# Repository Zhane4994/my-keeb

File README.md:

# My custom keeb for Fabricate

Hi! This keyboard was completely made and designed by my self with RMK software. This couldn't be done without Hack Club's KEEB doc's so huge shout out to them [Check it out here!](https://keeb.hackclub.com/docs/getting-started/) 
I also created a case on onshape, you can check it out [here](https://cad.onshape.com/documents/6c549647807777fa15118c8b/w/18eee8c51750e2c3ba516c3b/e/88b95604ab3b91696ed0ff4c?renderMode=0&uiState=6ae170e70fad28d43182f47b)
----------------------
 <-- PCB HERE

This is a mechanical keyboard that I built from scratch. 

Its a really weird layout. I decided that a delete key isn't really necessary but I still want the function keys. Its similar and close to a 75 percent, so I supposes its like 70%

*Every part of this was made by me and some clarification from AI*

Features:
- 
 - The Nice!View display
 - EC11E Rotary Encoder
 - 77 Switches
 - 3D Cad case

# Challenges
 - Remaking the PCB like 3 times.
 - Keeping prices low
 - Finishing before October (pls gimme free devboard)
 - Creating a custom footprint
 - Wiring the pcb

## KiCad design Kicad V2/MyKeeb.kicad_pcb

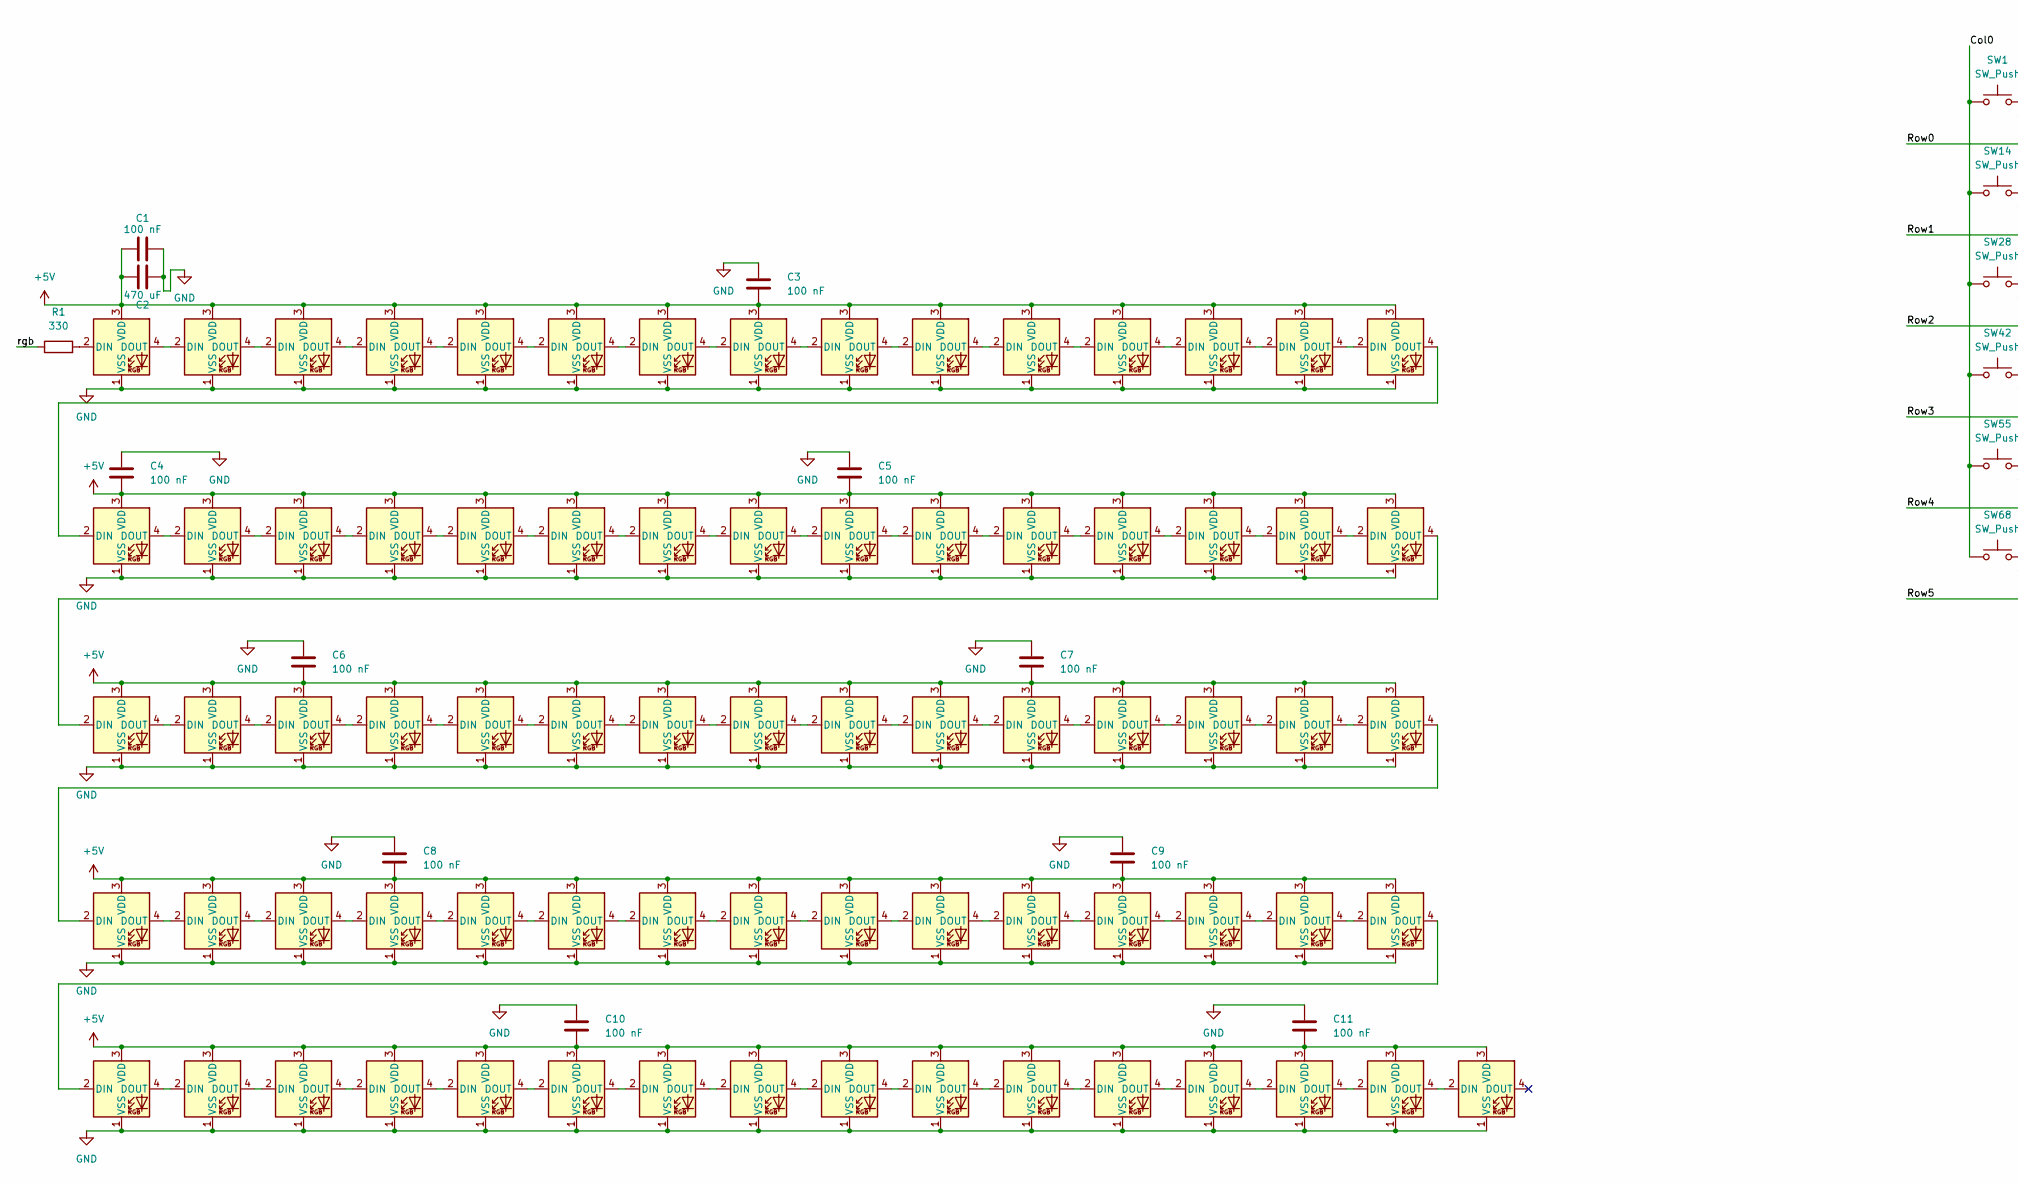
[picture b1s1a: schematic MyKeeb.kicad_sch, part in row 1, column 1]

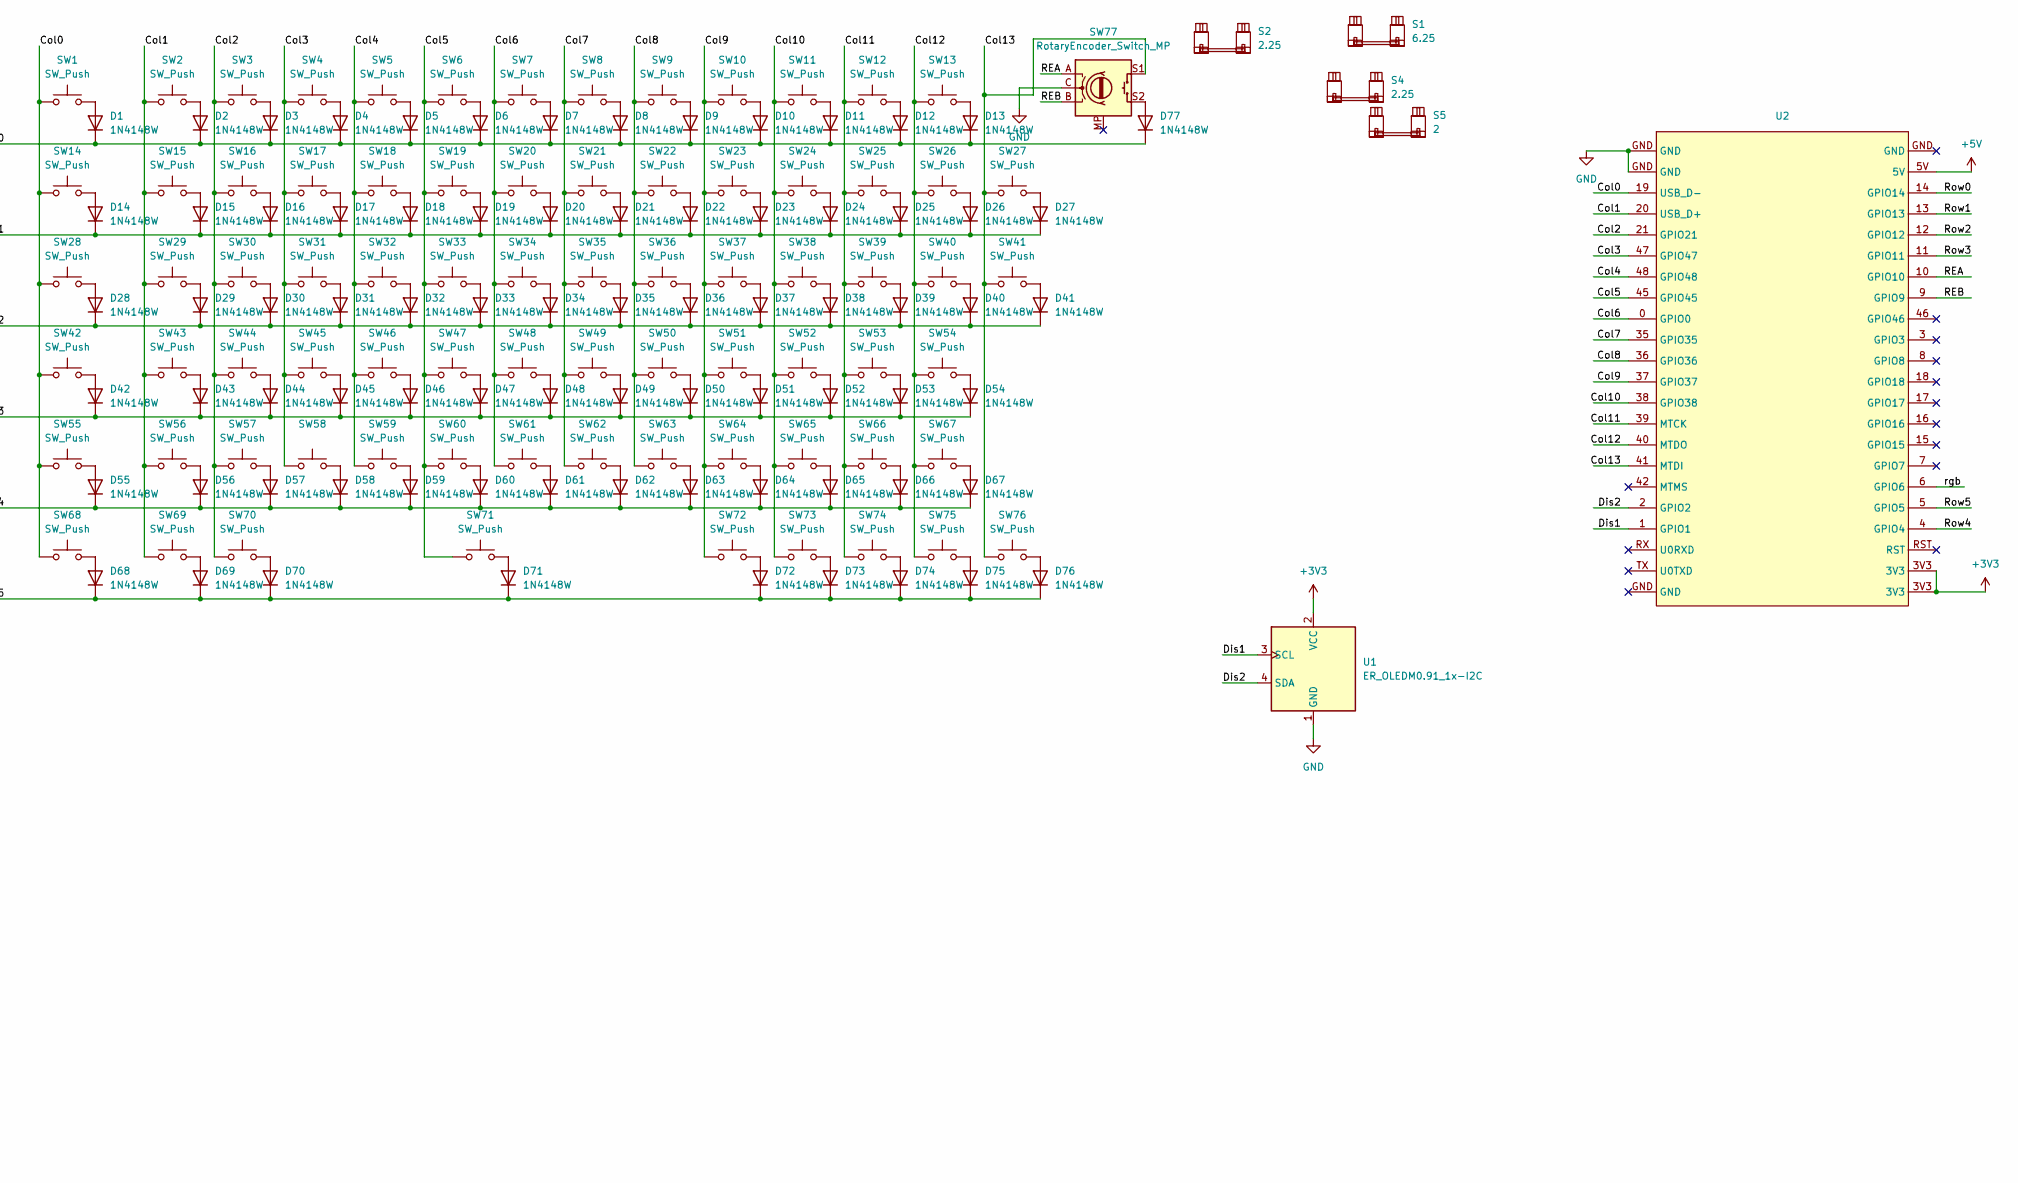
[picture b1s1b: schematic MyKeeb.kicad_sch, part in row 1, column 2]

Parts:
C1, C3, C4, C5, C6, C7, C8, C9, C10, C11: 100 nF; C_1206_3216Metric_Pad1.33x1.80mm_HandSolder
C2: 470 uF; C_Radial_D6.3mm_H7.0mm_P2.50mm
D1, D2, D3, D4, D5, D6, D7, D8, D9, D10, D11, D12, D13, D14, D15, D16, D17, D18, D19, D20, D21, D22, D23, D24, D25, D26, D27, D28, D29, D30, D31, D32, D33, D34, D35, D36, D37, D38, D39, D40, D41, D42, D43, D44, D45, D46, D47, D48, D49, D50, D51, D52, D53, D54, D55, D56, D57, D58, D59, D60, D61, D62, D63, D64, D65, D66, D67, D68, D69, D70, D71, D72, D73, D74, D75, D76, D77: 1N4148W; D_SOD-123
D78, D79, D80, D81, D82, D83, D84, D85, D86, D87, D88, D89, D90, D91, D92, D93, D94, D95, D96, D97, D98, D99, D100, D101, D102, D103, D104, D105, D106, D107, D108, D109, D110, D111, D112, D113, D114, D115, D116, D117, D118, D119, D120, D121, D122, D123, D124, D125, D126, D127, D128, D129, D130, D131, D132, D133, D134, D135, D136, D137, D138, D139, D140, D141, D142, D143, D144, D145, D146, D147, D148, D149, D150, D151, D152, D153: SK6812MINI-E; LED_MX_6028R
R1: 330; R_Axial_DIN0207_L6.3mm_D2.5mm_P10.16mm_Horizontal
S1: 6.25; STAB_MX_P_6.25u
S2, S4: 2.25; STAB_MX_2u
S5: 2; STAB_MX_2u
SW1, SW2, SW3, SW4, SW5, SW6, SW7, SW8, SW9, SW10, SW11, SW12, SW13, SW14, SW15, SW16, SW17, SW18, SW19, SW20, SW21, SW22, SW23, SW24, SW25, SW26, SW27, SW29, SW30, SW31, SW32, SW33, SW34, SW35, SW36, SW37, SW38, SW39, SW40, SW43, SW44, SW45, SW46, SW47, SW48, SW49, SW50, SW51, SW52, SW53, SW54, SW55, SW56, SW57, SW58, SW59, SW60, SW61, SW62, SW63, SW64, SW65, SW67, SW71, SW74, SW75, SW76: SW_Push; SW_MX_HS_KS-2P02B01-01_1u
SW28, SW41: SW_Push; SW_MX_HS_KS-2P02B01-01_1.5u
SW42, SW66: SW_Push; SW_MX_HS_KS-2P02B01-01_1.75u
SW68, SW69, SW70, SW72, SW73: SW_Push; SW_MX_HS_KS-2P02B01-01_1.25u
SW77: RotaryEncoder_Switch_MP; RotaryEncoder_Alps_EC11E-Switch_Vertical_H20mm_MountingHoles
U1: ER_OLEDM0.91_1x-I2C
U2: ESP32-S3-DevKit-N8R8

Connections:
+3V3: U1.2 (VCC), U2.3V3
+5V: C1.1, C2.1, C3.2, C4.2, C5.2, C6.2, C7.2, C8.2, C9.2, C10.2, C11.2, D78.3 (VDD), D79.3 (VDD), D80.3 (VDD), D81.3 (VDD), D82.3 (VDD), D83.3 (VDD), D84.3 (VDD), D85.3 (VDD), D86.3 (VDD), D87.3 (VDD), D88.3 (VDD), D89.3 (VDD), D90.3 (VDD), D91.3 (VDD), D92.3 (VDD), D93.3 (VDD), D94.3 (VDD), D95.3 (VDD), D96.3 (VDD), D97.3 (VDD), D98.3 (VDD), D99.3 (VDD), D100.3 (VDD), D101.3 (VDD), D102.3 (VDD), D103.3 (VDD), D104.3 (VDD), D105.3 (VDD), D106.3 (VDD), D107.3 (VDD), D108.3 (VDD), D109.3 (VDD), D110.3 (VDD), D111.3 (VDD), D112.3 (VDD), D113.3 (VDD), D114.3 (VDD), D115.3 (VDD), D116.3 (VDD), D117.3 (VDD), D118.3 (VDD), D119.3 (VDD), D120.3 (VDD), D121.3 (VDD), D122.3 (VDD), D123.3 (VDD), D124.3 (VDD), D125.3 (VDD), D126.3 (VDD), D127.3 (VDD), D128.3 (VDD), D129.3 (VDD), D130.3 (VDD), D131.3 (VDD), D132.3 (VDD), D133.3 (VDD), D134.3 (VDD), D135.3 (VDD), D136.3 (VDD), D137.3 (VDD), D138.3 (VDD), D139.3 (VDD), D140.3 (VDD), D141.3 (VDD), D142.3 (VDD), D143.3 (VDD), D144.3 (VDD), D145.3 (VDD), D146.3 (VDD), D147.3 (VDD), D148.3 (VDD), D149.3 (VDD), D150.3 (VDD), D151.3 (VDD), D152.3 (VDD), D153.3 (VDD), U2.5V
/Col0: SW1.1, SW14.1, SW28.1, SW42.1, SW55.1, SW68.1, U2.19 (USB_D-)
/Col1: SW2.1, SW15.1, SW29.1, SW43.1, SW56.1, SW69.1, U2.20 (USB_D+)
/Col2: SW3.1, SW16.1, SW30.1, SW44.1, SW57.1, SW70.1, U2.21 (GPIO21)
/Col3: SW4.1, SW17.1, SW31.1, SW45.1, SW58.1, U2.47 (GPIO47)
/Col4: SW5.1, SW18.1, SW32.1, SW46.1, SW59.1, U2.48 (GPIO48)
/Col5: SW6.1, SW19.1, SW33.1, SW47.1, SW60.1, SW71.1, U2.45 (GPIO45)
/Col6: SW7.1, SW20.1, SW34.1, SW48.1, SW61.1, U2.0 (GPIO0)
/Col7: SW8.1, SW21.1, SW35.1, SW49.1, SW62.1, U2.35 (GPIO35)
/Col8: SW9.1, SW22.1, SW36.1, SW50.1, SW63.1, U2.36 (GPIO36)
/Col9: SW10.1, SW23.1, SW37.1, SW51.1, SW64.1, SW72.1, U2.37 (GPIO37)
/Col10: SW11.1, SW24.1, SW38.1, SW52.1, SW65.1, SW73.1, U2.38 (GPIO38)
/Col11: SW12.1, SW25.1, SW39.1, SW53.1, SW66.1, SW74.1, U2.39 (MTCK)
/Col12: SW13.1, SW26.1, SW40.1, SW54.1, SW67.1, SW75.1, U2.40 (MTDO)
/Col13: SW27.1, SW41.1, SW76.1, SW77.S1, U2.41 (MTDI)
/Dis1: U1.3 (SCL), U2.1 (GPIO1)
/Dis2: U1.4 (SDA), U2.2 (GPIO2)
/REA: SW77.A, U2.10 (GPIO10)
/REB: SW77.B, U2.9 (GPIO9)
/Row0: D1.1 (K), D2.1 (K), D3.1 (K), D4.1 (K), D5.1 (K), D6.1 (K), D7.1 (K), D8.1 (K), D9.1 (K), D10.1 (K), D11.1 (K), D12.1 (K), D13.1 (K), D77.1 (K), U2.14 (GPIO14)
/Row1: D14.1 (K), D15.1 (K), D16.1 (K), D17.1 (K), D18.1 (K), D19.1 (K), D20.1 (K), D21.1 (K), D22.1 (K), D23.1 (K), D24.1 (K), D25.1 (K), D26.1 (K), D27.1 (K), U2.13 (GPIO13)
/Row2: D28.1 (K), D29.1 (K), D30.1 (K), D31.1 (K), D32.1 (K), D33.1 (K), D34.1 (K), D35.1 (K), D36.1 (K), D37.1 (K), D38.1 (K), D39.1 (K), D40.1 (K), D41.1 (K), U2.12 (GPIO12)
/Row3: D42.1 (K), D43.1 (K), D44.1 (K), D45.1 (K), D46.1 (K), D47.1 (K), D48.1 (K), D49.1 (K), D50.1 (K), D51.1 (K), D52.1 (K), D53.1 (K), D54.1 (K), U2.11 (GPIO11)
/Row4: D55.1 (K), D56.1 (K), D57.1 (K), D58.1 (K), D59.1 (K), D60.1 (K), D61.1 (K), D62.1 (K), D63.1 (K), D64.1 (K), D65.1 (K), D66.1 (K), D67.1 (K), U2.4 (GPIO4)
/Row5: D68.1 (K), D69.1 (K), D70.1 (K), D71.1 (K), D72.1 (K), D73.1 (K), D74.1 (K), D75.1 (K), D76.1 (K), U2.5 (GPIO5)
/rgb: R1.1, U2.6 (GPIO6)
GND: C1.2, C2.2, C3.1, C4.1, C5.1, C6.1, C7.1, C8.1, C9.1, C10.1, C11.1, D78.1 (VSS), D79.1 (VSS), D80.1 (VSS), D81.1 (VSS), D82.1 (VSS), D83.1 (VSS), D84.1 (VSS), D85.1 (VSS), D86.1 (VSS), D87.1 (VSS), D88.1 (VSS), D89.1 (VSS), D90.1 (VSS), D91.1 (VSS), D92.1 (VSS), D93.1 (VSS), D94.1 (VSS), D95.1 (VSS), D96.1 (VSS), D97.1 (VSS), D98.1 (VSS), D99.1 (VSS), D100.1 (VSS), D101.1 (VSS), D102.1 (VSS), D103.1 (VSS), D104.1 (VSS), D105.1 (VSS), D106.1 (VSS), D107.1 (VSS), D108.1 (VSS), D109.1 (VSS), D110.1 (VSS), D111.1 (VSS), D112.1 (VSS), D113.1 (VSS), D114.1 (VSS), D115.1 (VSS), D116.1 (VSS), D117.1 (VSS), D118.1 (VSS), D119.1 (VSS), D120.1 (VSS), D121.1 (VSS), D122.1 (VSS), D123.1 (VSS), D124.1 (VSS), D125.1 (VSS), D126.1 (VSS), D127.1 (VSS), D128.1 (VSS), D129.1 (VSS), D130.1 (VSS), D131.1 (VSS), D132.1 (VSS), D133.1 (VSS), D134.1 (VSS), D135.1 (VSS), D136.1 (VSS), D137.1 (VSS), D138.1 (VSS), D139.1 (VSS), D140.1 (VSS), D141.1 (VSS), D142.1 (VSS), D143.1 (VSS), D144.1 (VSS), D145.1 (VSS), D146.1 (VSS), D147.1 (VSS), D148.1 (VSS), D149.1 (VSS), D150.1 (VSS), D151.1 (VSS), D152.1 (VSS), D153.1 (VSS), SW77.C, U1.1 (GND), U2.GND
unnamed: D1.2 (A), SW1.2
unnamed: D2.2 (A), SW2.2
unnamed: D3.2 (A), SW3.2
unnamed: D4.2 (A), SW4.2
unnamed: D5.2 (A), SW5.2
unnamed: D6.2 (A), SW6.2
unnamed: D7.2 (A), SW7.2
unnamed: D8.2 (A), SW8.2
unnamed: D9.2 (A), SW9.2
unnamed: D10.2 (A), SW10.2
unnamed: D11.2 (A), SW11.2
unnamed: D12.2 (A), SW12.2
unnamed: D13.2 (A), SW13.2
unnamed: D14.2 (A), SW14.2
unnamed: D15.2 (A), SW15.2
unnamed: D16.2 (A), SW16.2
unnamed: D17.2 (A), SW17.2
unnamed: D18.2 (A), SW18.2
unnamed: D19.2 (A), SW19.2
unnamed: D20.2 (A), SW20.2
unnamed: D21.2 (A), SW21.2
unnamed: D22.2 (A), SW22.2
unnamed: D23.2 (A), SW23.2
unnamed: D24.2 (A), SW24.2
unnamed: D25.2 (A), SW25.2
unnamed: D26.2 (A), SW26.2
unnamed: D27.2 (A), SW27.2
unnamed: D28.2 (A), SW28.2
unnamed: D29.2 (A), SW29.2
unnamed: D30.2 (A), SW30.2
unnamed: D31.2 (A), SW31.2
unnamed: D32.2 (A), SW32.2
unnamed: D33.2 (A), SW33.2
unnamed: D34.2 (A), SW34.2
unnamed: D35.2 (A), SW35.2
unnamed: D36.2 (A), SW36.2
unnamed: D37.2 (A), SW37.2
unnamed: D38.2 (A), SW38.2
unnamed: D39.2 (A), SW39.2
unnamed: D40.2 (A), SW40.2
unnamed: D41.2 (A), SW41.2
unnamed: D42.2 (A), SW42.2
unnamed: D43.2 (A), SW43.2
unnamed: D44.2 (A), SW44.2
unnamed: D45.2 (A), SW45.2
unnamed: D46.2 (A), SW46.2
unnamed: D47.2 (A), SW47.2
unnamed: D48.2 (A), SW48.2
unnamed: D49.2 (A), SW49.2
unnamed: D50.2 (A), SW50.2
unnamed: D51.2 (A), SW51.2
unnamed: D52.2 (A), SW52.2
unnamed: D53.2 (A), SW53.2
unnamed: D54.2 (A), SW54.2
unnamed: D55.2 (A), SW55.2
unnamed: D56.2 (A), SW56.2
unnamed: D57.2 (A), SW57.2
unnamed: D58.2 (A), SW58.2
unnamed: D59.2 (A), SW59.2
unnamed: D60.2 (A), SW60.2
unnamed: D61.2 (A), SW61.2
unnamed: D62.2 (A), SW62.2
unnamed: D63.2 (A), SW63.2
unnamed: D64.2 (A), SW64.2
unnamed: D65.2 (A), SW65.2
unnamed: D66.2 (A), SW66.2
unnamed: D67.2 (A), SW67.2
unnamed: D68.2 (A), SW68.2
unnamed: D69.2 (A), SW69.2
unnamed: D70.2 (A), SW70.2
unnamed: D71.2 (A), SW71.2
unnamed: D72.2 (A), SW72.2
unnamed: D73.2 (A), SW73.2
unnamed: D74.2 (A), SW74.2
unnamed: D75.2 (A), SW75.2
unnamed: D76.2 (A), SW76.2
unnamed: D77.2 (A), SW77.S2
unnamed: D78.2 (DIN), R1.2
unnamed: D78.4 (DOUT), D79.2 (DIN)
unnamed: D79.4 (DOUT), D80.2 (DIN)
unnamed: D80.4 (DOUT), D81.2 (DIN)
unnamed: D81.4 (DOUT), D82.2 (DIN)
unnamed: D82.4 (DOUT), D83.2 (DIN)
unnamed: D83.4 (DOUT), D84.2 (DIN)
unnamed: D84.4 (DOUT), D85.2 (DIN)
unnamed: D85.4 (DOUT), D86.2 (DIN)
unnamed: D86.4 (DOUT), D87.2 (DIN)
unnamed: D87.4 (DOUT), D88.2 (DIN)
unnamed: D88.4 (DOUT), D89.2 (DIN)
unnamed: D89.4 (DOUT), D90.2 (DIN)
unnamed: D90.4 (DOUT), D91.2 (DIN)
unnamed: D91.4 (DOUT), D92.2 (DIN)
unnamed: D92.4 (DOUT), D93.2 (DIN)
unnamed: D93.4 (DOUT), D94.2 (DIN)
unnamed: D94.4 (DOUT), D95.2 (DIN)
unnamed: D95.4 (DOUT), D96.2 (DIN)
unnamed: D96.4 (DOUT), D97.2 (DIN)
unnamed: D97.4 (DOUT), D98.2 (DIN)
unnamed: D98.4 (DOUT), D99.2 (DIN)
unnamed: D99.4 (DOUT), D100.2 (DIN)
unnamed: D100.4 (DOUT), D101.2 (DIN)
unnamed: D101.4 (DOUT), D102.2 (DIN)
unnamed: D102.4 (DOUT), D103.2 (DIN)
unnamed: D103.4 (DOUT), D104.2 (DIN)
unnamed: D104.4 (DOUT), D105.2 (DIN)
unnamed: D105.4 (DOUT), D106.2 (DIN)
unnamed: D106.4 (DOUT), D107.2 (DIN)
unnamed: D107.4 (DOUT), D108.2 (DIN)
unnamed: D108.4 (DOUT), D109.2 (DIN)
unnamed: D109.4 (DOUT), D110.2 (DIN)
unnamed: D110.4 (DOUT), D111.2 (DIN)
unnamed: D111.4 (DOUT), D112.2 (DIN)
unnamed: D112.4 (DOUT), D113.2 (DIN)
unnamed: D113.4 (DOUT), D114.2 (DIN)
unnamed: D114.4 (DOUT), D115.2 (DIN)
unnamed: D115.4 (DOUT), D116.2 (DIN)
unnamed: D116.4 (DOUT), D117.2 (DIN)
unnamed: D117.4 (DOUT), D118.2 (DIN)
unnamed: D118.4 (DOUT), D119.2 (DIN)
unnamed: D119.4 (DOUT), D120.2 (DIN)
unnamed: D120.4 (DOUT), D121.2 (DIN)
unnamed: D121.4 (DOUT), D122.2 (DIN)
unnamed: D122.4 (DOUT), D123.2 (DIN)
unnamed: D123.4 (DOUT), D124.2 (DIN)
unnamed: D124.4 (DOUT), D125.2 (DIN)
unnamed: D125.4 (DOUT), D126.2 (DIN)
unnamed: D126.4 (DOUT), D127.2 (DIN)
unnamed: D127.4 (DOUT), D128.2 (DIN)
unnamed: D128.4 (DOUT), D129.2 (DIN)
unnamed: D129.4 (DOUT), D130.2 (DIN)
unnamed: D130.4 (DOUT), D131.2 (DIN)
unnamed: D131.4 (DOUT), D132.2 (DIN)
unnamed: D132.4 (DOUT), D133.2 (DIN)
unnamed: D133.4 (DOUT), D134.2 (DIN)
unnamed: D134.4 (DOUT), D135.2 (DIN)
unnamed: D135.4 (DOUT), D136.2 (DIN)
unnamed: D136.4 (DOUT), D137.2 (DIN)
unnamed: D137.4 (DOUT), D138.2 (DIN)
unnamed: D138.4 (DOUT), D139.2 (DIN)
unnamed: D139.4 (DOUT), D140.2 (DIN)
unnamed: D140.4 (DOUT), D141.2 (DIN)
unnamed: D141.4 (DOUT), D142.2 (DIN)
unnamed: D142.4 (DOUT), D143.2 (DIN)
unnamed: D143.4 (DOUT), D144.2 (DIN)
unnamed: D144.4 (DOUT), D145.2 (DIN)
unnamed: D145.4 (DOUT), D146.2 (DIN)
unnamed: D146.4 (DOUT), D147.2 (DIN)
unnamed: D147.4 (DOUT), D148.2 (DIN)
unnamed: D148.4 (DOUT), D149.2 (DIN)
unnamed: D149.4 (DOUT), D150.2 (DIN)
unnamed: D150.4 (DOUT), D151.2 (DIN)
unnamed: D151.4 (DOUT), D152.2 (DIN)
unnamed: D152.4 (DOUT), D153.2 (DIN)

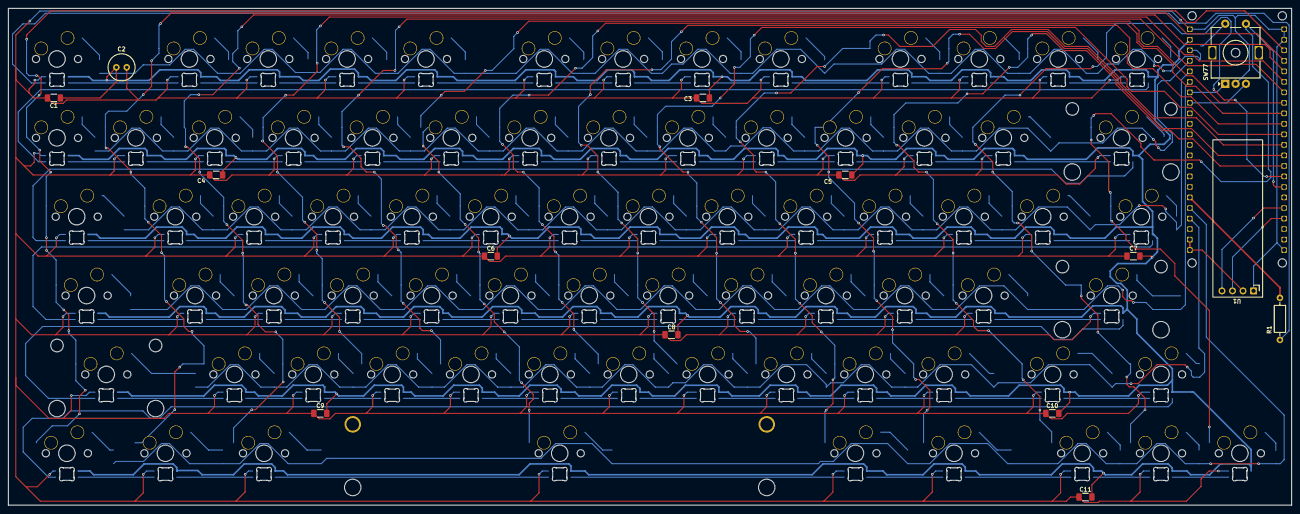
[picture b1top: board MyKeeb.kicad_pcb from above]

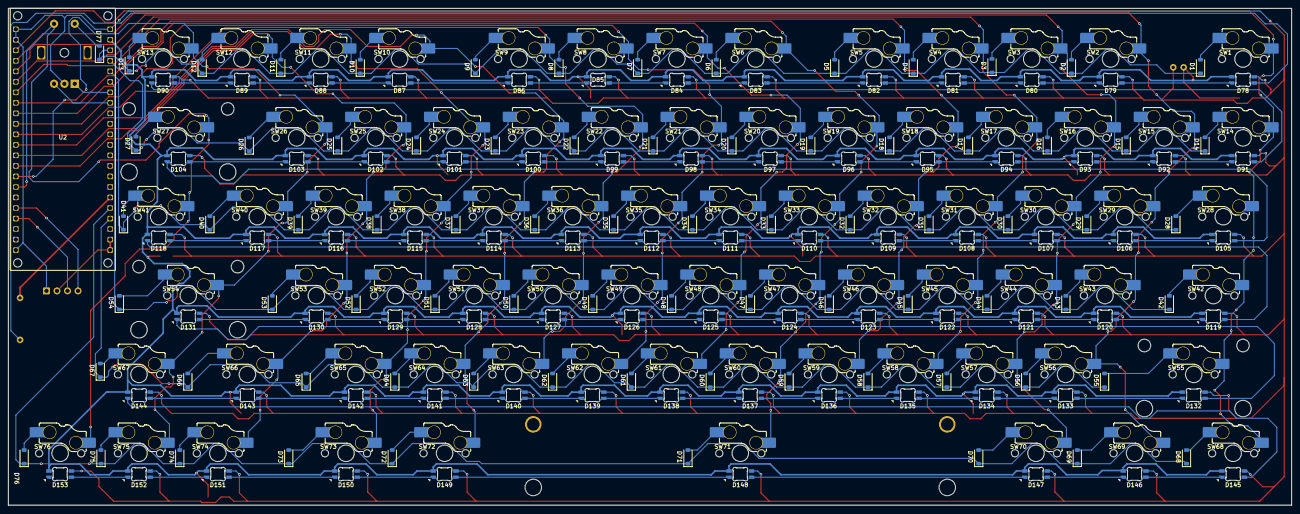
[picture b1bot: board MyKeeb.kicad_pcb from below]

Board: 2 copper layers, 310.0 x 120.0 mm, 248 parts (234 on the bottom side), 181 nets.
